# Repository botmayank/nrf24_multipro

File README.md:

# nrf24_multipro_h8_pc
nRF24L01 multi-protocol RC transmitter project being used for JJRC/Eachine H8 mini to control over Serial. This project aims to develop a USB dongle to control the H8 directly from the PC using the nRF24L01+ module and later expand to control and/or charge multiple quadcopters with this custom hardware based on the Arduino Leonardo (Atmega32u4).

The main Arduino code is in the nRF24_multipro folder with the main sketch being nRF24_multipro.ino. The script to control the quad over serial is serial_test.py while the board files for the Quadstick are in the hardware_design folder.

This project is based on the work of perrystao:
https://github.com/perrytsao/nrf24_cx10_pc

which in turn is based upon the awesome nrf24_multipro project by goebish:
https://github.com/goebish/nrf24_multipro

Arduino Nano and nRF24L01+ Module on perfboard to control Syma X20

## Connections

| Arduino Uno/Nano    | NRF24L01+ Module               | nRF Pin No.   |
|---------------------|--------------------------------|---------------|
| GND                 | GND                            | 1             |
| 3.3V                | VCC                            | 2             |
| D5 (Digital 5)      | CE                             | 3             |
| A1 (Analog 1)       | CSN                            | 4             |
| D4 (Digital 4)      | SCK                            | 5             |
| D3 (Digital 3)      | MOSI                           | 6             |
| A0 (Analog 0)       | MISO                           | 7             |
| Not Used            | IRQ                            | 8             |

# Configure

run `export PYTHONPATH=.` at the root of the project folder to run the files from terminal. 
Why this isn't needed on Pycharm is because it sets it for you.

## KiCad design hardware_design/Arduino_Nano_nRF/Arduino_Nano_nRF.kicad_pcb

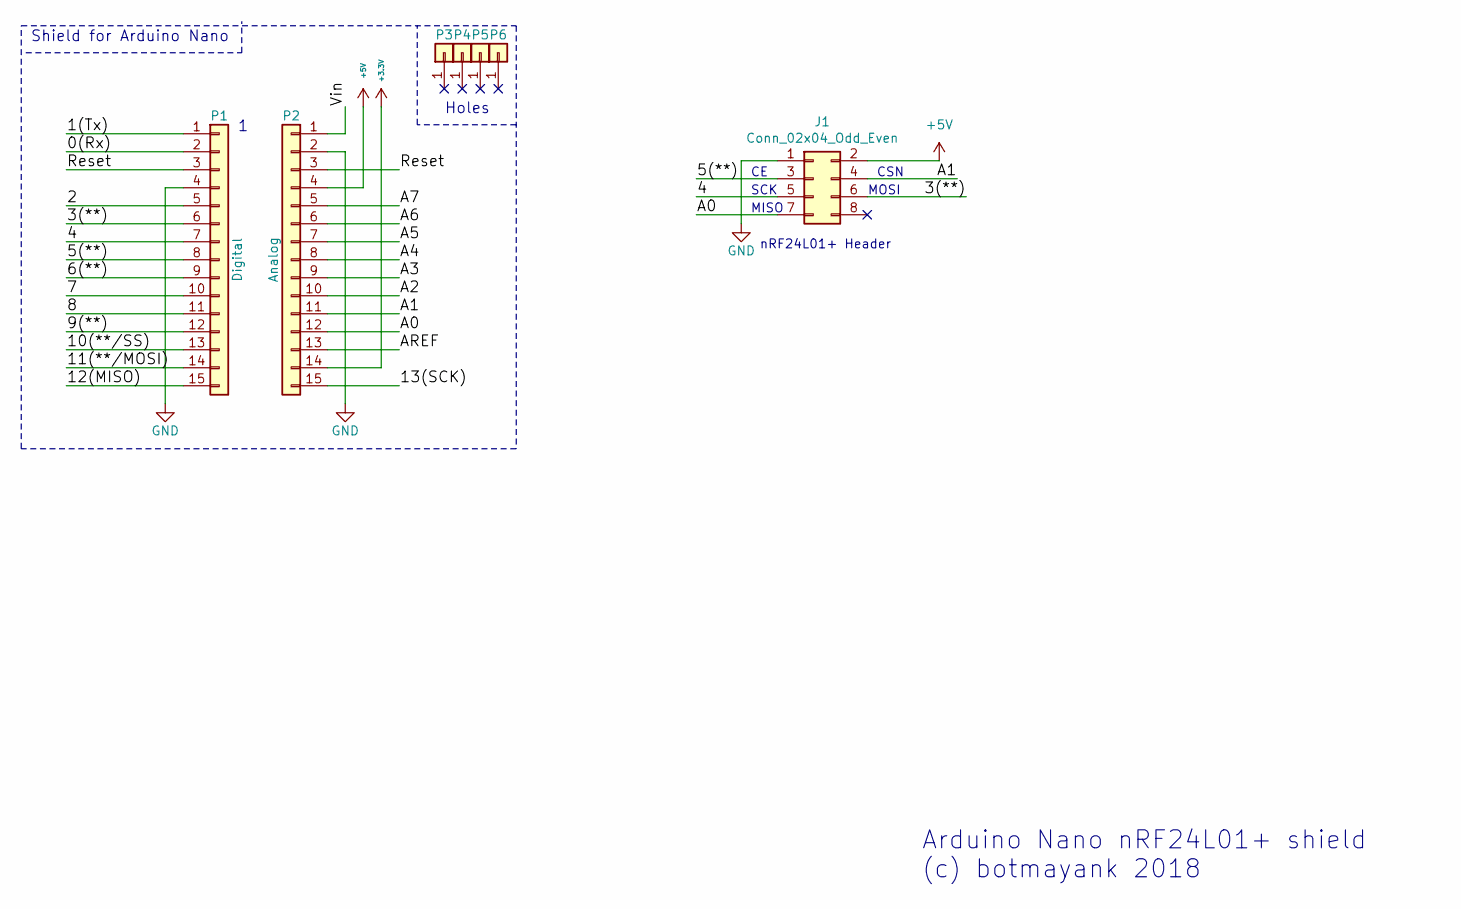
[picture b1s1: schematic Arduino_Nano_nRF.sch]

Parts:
J1: Conn_02x04_Odd_Even; PinHeader_2x04_P2.54mm_Vertical
P1: Digital; Socket_Strip_Arduino_1x15
P2: Analog; Socket_Strip_Arduino_1x15
P3, P4, P5, P6: CONN_01X01; 1pin_Nano

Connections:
+3V3: P2.14
+5V: J1.2, P2.4
/0(Rx): P1.2
/1(Tx): P1.1
/2: P1.5
/3(**): J1.6, P1.6
/4: J1.5, P1.7
/5(**): J1.3, P1.8
/6(**): P1.9
/7: P1.10
/8: P1.11
/9(**): P1.12
/10(**/SS): P1.13
/11(**/MOSI): P1.14
/12(MISO): P1.15
/13(SCK): P2.15
/A0: J1.7, P2.12
/A1: J1.4, P2.11
/A2: P2.10
/A3: P2.9
/A4: P2.8
/A5: P2.7
/A6: P2.6
/A7: P2.5
/AREF: P2.13
/Reset: P1.3, P2.3
/Vin: P2.1
GND: J1.1, P1.4, P2.2

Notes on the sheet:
Holes
Shield for Arduino Nano
Arduino Nano nRF24L01+ shield (c) botmayank 2018
nRF24L01+ Header
CSN
SCK
MOSI
MISO

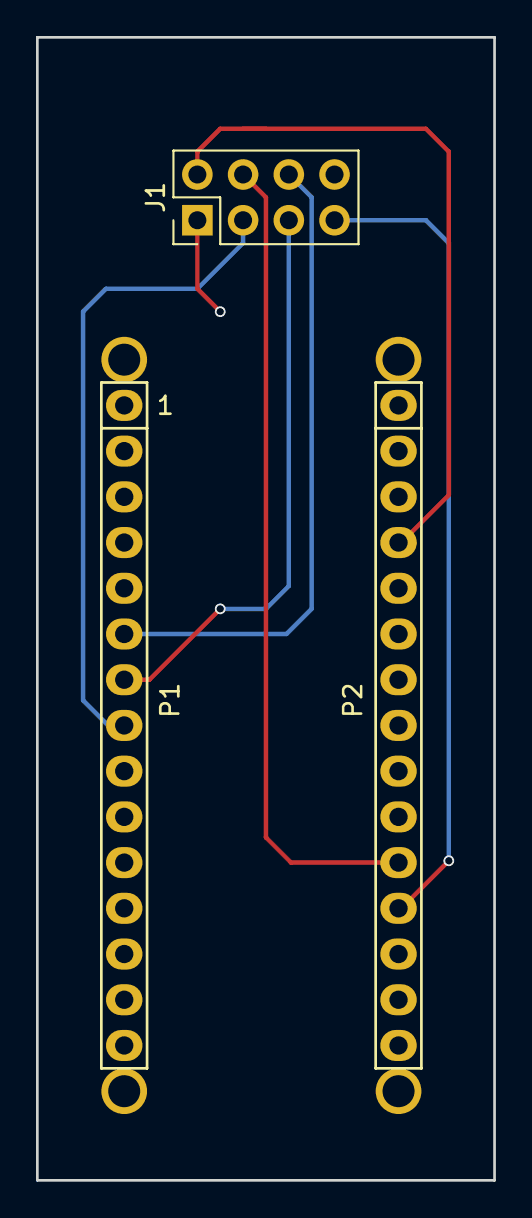
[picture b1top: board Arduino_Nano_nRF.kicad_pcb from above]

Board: 2 copper layers, 25.4 x 63.5 mm, 7 parts (0 on the bottom side), 8 nets.

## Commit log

2017-11-10 Init working, bind not done
2017-11-14 Modification for h8 and serial python script
2017-11-14 Readme updated
2017-11-14 Eagle Schematic basic from Arduino Leonardo
2017-11-14 Added photo of setup
2017-11-25 Modified for Linux implementing msvcrt functions using sys calls
2017-11-25 arduino sketch moved to nrf24_multipro_h8
2017-11-25 Working modified perrytsao project for h8 mini
2018-01-03 added eagle layout
2018-01-10 Re-positioned all components for USB and Analog parts to top layer for easier reflow
2018-09-03 Added datasheets for quadstick
2018-09-03 Cleaned up main arduino script for Syma, JJRC H8 and H8 3D
2018-09-03 Changed serial port
2018-09-03 Updated README.md for Syma X20
2018-09-03 Correct relative jpg link in README.md
2018-09-03 Added .jpeg extensions
2018-09-08 rc_scripts for controlling using curses
2018-09-08 Throttle control added with special keys
2018-09-09 Added all controls roll, pitch, yaw
2018-09-09 Fixed pitch bug in update_input
2018-09-14 Update gitignore for python + intellij
2018-09-14 Decoupled keyboard input and flight controller
2018-09-14 Serial Syma cleanup
2018-09-14 Add aruco finder
    todo: add the camera calib package if there'll be one
2018-09-14 Add calibration script
    Write to yaml
2018-09-14 Add aruco generator helper
2018-09-14 Add capture images file
    Super surprised I don't find this written in python that I can take off
    the shelf
    Will later make a single camera open/close class
2018-09-14 Basic bang-bang controller for height
2018-09-14 Added optional delta args to exposed flight methods in SymaController
2018-09-14 Set physical dimension for aruco markers
2018-09-14 Added README for auto_flight
2018-09-15 Working throttle control
    There was a silly mistake in calculating the distance between the
    corners sigh. Should ideally use the tvec and rvec provided by
    estimatePose
    Still very primitive.
    The code's kinda messy right now - but we'll clean it up
2018-09-15 Integrate aruco finder into control
    todo - cap the max and min received from the aruco finder
2018-09-15 Add joystick controller using pygame
2018-09-15 Rename manual input to keyboard input
2018-09-15 Add commands for relative values of quad controls
    These will allow for exact values instead of changing using a gain or
    delta parameter
2018-09-15 Repackaging for better understanding of what we're doing
    - manual inputs using keyboard and joystick
    - autonomous inputs using camera
2018-09-15 Fly quad with joystick works
    figured out that setting roll pitch directly (range -1 ro 1) works a lot
    better than incrementing it as in the case of throttle. In that too, the
    max and min values don't exactly hold - figured out what their acromode
    effectively does; sends higher threshold of the RPY values.
    Throttle it only makes sense to be changing things with deltas.
    Also, keeping the quad stuck the rope kinda fucks it up.
2018-09-16 Add commands for shut down and start
2018-09-16 Add acro-mode using r1 and r2 for better control
    I think the RPY part is sorted; still not happy with the throttle
    though. It doesn't seem to stick to how much I ask it to - even though
    we're changing the throttle only using deltas. Steady state is probably
    a value lower than the one actually set
2018-09-16 Update aruco_finder to read from redmi calib + static video
    Todo, later will make this pick cameras and calibs properly, just
    hardcoding badly right now cuz I want to see results
2018-09-16 Show detection rate in aruco finder
2018-09-18 Try different aruco parameters
2018-09-20 Controller works perfectly + use a simple off the shelf tracker
    The opencv tracker works moderately well. Will use this atm.
    Except I used some shitty hardcoding there.
2018-09-20 Move camera things to camerasrc
2018-09-21 Draw proper bounding box on quad copter while tracking
2018-09-22 Draw yaw angle on the frame
2018-09-23 Add Pose class and use that to encapsulate tracking / detections
2018-09-23 Add initial try at center maintain
    This doesn't work as easyily as I thought it would.
    Realized I'll need a lot of black chart paper + make a controller and
    figure out what to do one by one
2018-09-23 Simple shield for nRF module and Arduino Nano in KiCAD
    (cherry picked from commit f9ca69a161c57fbc2aba25abcecc165ee3b5d1f5)
2018-09-23 Run aruco as a child process and pipe its output
    This is a very naive attempt but things seem to be shaping up.
    The detection rate is still low - mostly because the paper I'm using is
    shining. Another thing that I have to do is find the rotation based on
    tracked box
2018-09-24 Calculate yaw based on contour detection
    Basically needed to know yaw when the drone isn't detected by aruco
2018-09-28 Completed layout for nRF Dongle
